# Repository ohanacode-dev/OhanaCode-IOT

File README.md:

**OhanaCode-IOT**

This is my personal Internet Of Things set of projects. It is intended as a low budget home automation system. 
I am building my own WiFi controlled devices and controlling them through their own web interface. 
Most devices can act as an access point or a client device on a WiFi network. After it connects to your home network, 
it gets difficult to find its IP address if it is dynamically alocated, so I also provided an Android app to list all devices on the same network. 
Every device responds to an UDP broadcast string "ujagaga ping" via TCP socket. 
There is also an implemented Over The Air update. 
Most projects are build using Arduino studio and an **ESP8266** device. I am using **Wemos D1 mini** and **ESP-12** devices.

NOTE: this is still work in progress. Most of the projects are functional, but I still want to improove them.
Most projects support "Over The Air" update, but it does sometimes crash, so you will still ocasionally need the wired connection.
The whole project is in the process if adding mqtt support in order to connect to the new addition "iot-portal". This way you can controll them all from a single device.

## Latest Changes

- Fixed LED_lamp_RGB project to use the iot-portal.

- Fixed "switch" project to use the iot-portal. Had to remove udp ping as it caused connection issues.

- Added iot-portal to be ran on a computer like raspberry pi zero. All devices should report to it so it can be used as a central point of access. 

---

## Using the code

Every device has an Arduino sketch in it's own folder, so open the sketch in **Arduino studio** and set the proper board and parameters for your board, compile and program. 
For the web interface some projects use SPIFFS library to upload HTML, CSS, JS files to virtual file system in the SPI flash. To upload these files, you need **Arduino ESP8266 filesystem uploader**. It integrates in your Arduino studio and adds an entry in the **Tools** menu. To install it, follow instructions from: https://github.com/esp8266/arduino-esp8266fs-plugin
After that you might want to open the **serial monitor** to see the debug messages for more info. 
You can then connect to devices access point, use your browser to control and configure it. 
Project is still in development. I believe that the switch, LED_lamp, LED_lamp_RGB, lazy_control and OC-IOT-Browser have reached their final state and are ready for use. Other projects are usable, but will be refactored a lot. Reffer to each projects **readme** for current status. 

---

## lazy_control

A python multimedial server for your PC. Should work on windows and linux.

---

## LED_lamp

Just a single color LED light controll device. 

---

## LED_lamp_RGB

An RGB LED lamp controll.

---

## NTP_clock

A stepper motor control using an NTP server for time sync. This will drive two clock hands to show time.

---

## NTP_timer

An NTP synchronized timer to activate a relay.

---

## thermometer

A thermometer using either low temperature probe **DS18B20** or a high temperature thermopar probe module with **max6675**.

---

## thermostat

A thermometer project expanded with a relay driving capability.

---

## IOTBrowser

An Android application to list and provide a quick access to all **Ohana-IOT** devices on the same network.

---

## ohana-radio

A linux internet radio with a web interface.

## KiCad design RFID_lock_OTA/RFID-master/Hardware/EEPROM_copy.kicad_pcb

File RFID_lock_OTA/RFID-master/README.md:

RFID reader project for AtTiny2313 using MIFARE RFID-RC522 spi module

The RFID library is based on Addicore arduino library. I re-wrote it as pure C library and removed 
everything not esential to bare reading of an RFID TAG id to reduce the code size.

The initial commit contains a basic example of reading a tag and outputting the 4 bytes of id to UART.
The latest commit contains:
- full RFID example which can record up to 32 tag ids and unlock an electromagnetic lock
- EEPROM reader device which can be used to record the RFID readers memory and write it back on command
so that re-distributing codes between multiple locks can be simpified
- Linux and Windows console applications for administrating tag ids using either the EEPROM copy device 
or the RFID reader directly.

more details will be in the doc folder.

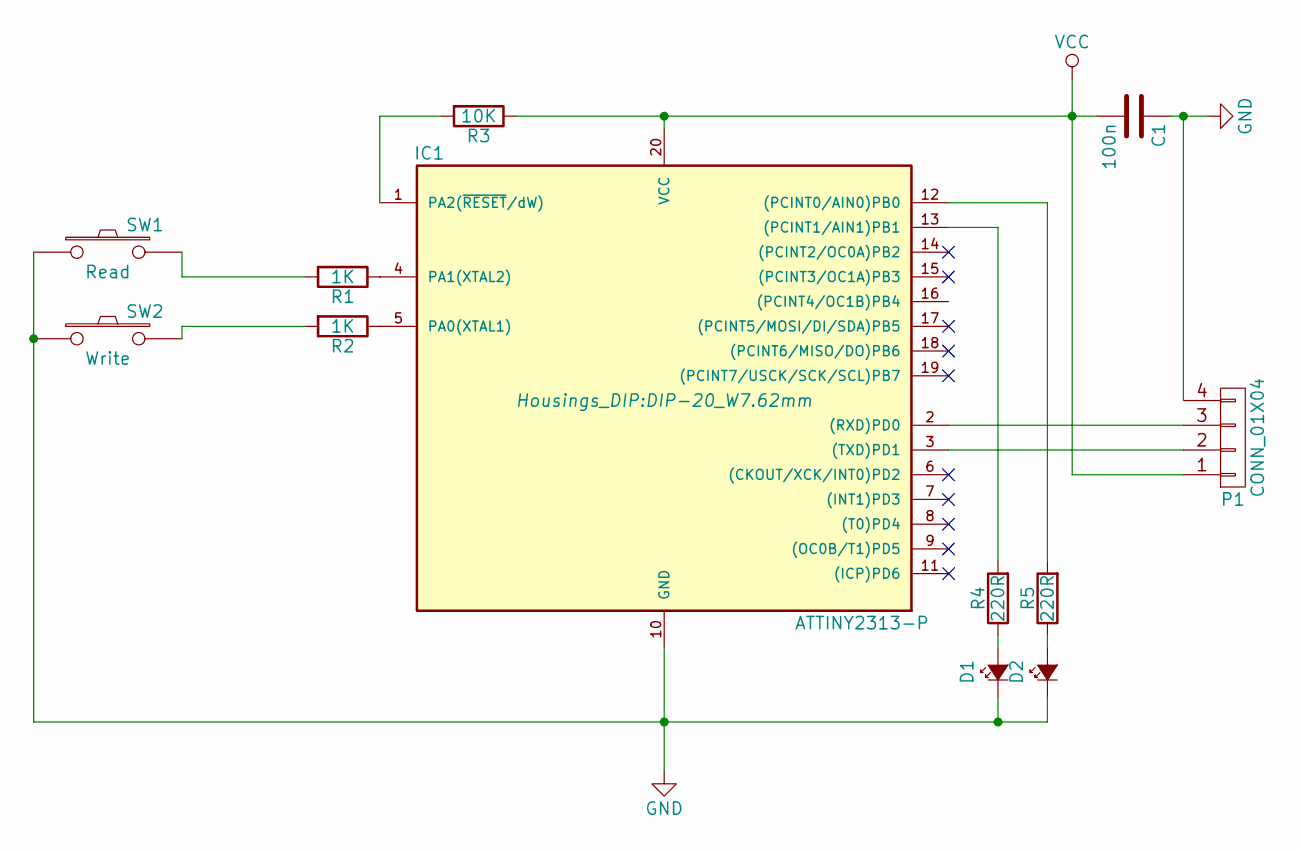
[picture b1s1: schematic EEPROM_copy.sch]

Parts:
C1: 100n; C_0805_HandSoldering
D1, D2: Led_Small; LED-3MM
IC1: ATTINY2313-P; DIP-20_W7.62mm
P1: CONN_01X04; Socket_Strip_Angled_1x04
R1, R2: 1K; R_0805
R3: 10K; R_0805
R4, R5: 220R; R_0805
SW1: Read; Micro_sw_1
SW2: Write; Micro_sw_1

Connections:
GND: C1.1, D1.1 (K), D2.1 (K), IC1.10 (GND), P1.4, SW1.1, SW2.1
unnamed: D1.2 (A), R4.1
unnamed: D2.2 (A), R5.1
unnamed: IC1.1 (PA2(~RESET~/dW)), R3.2
unnamed: IC1.2 ((RXD)PD0), P1.3
unnamed: IC1.3 ((TXD)PD1), P1.2
unnamed: IC1.4 (PA1(XTAL2)), R1.1
unnamed: IC1.5 (PA0(XTAL1)), R2.1
unnamed: IC1.12 ((PCINT0/AIN0)PB0), R5.2
unnamed: IC1.13 ((PCINT1/AIN1)PB1), R4.2
unnamed: R1.2, SW1.2
unnamed: R2.2, SW2.2
VCC: C1.2, IC1.20 (VCC), P1.1, R3.1

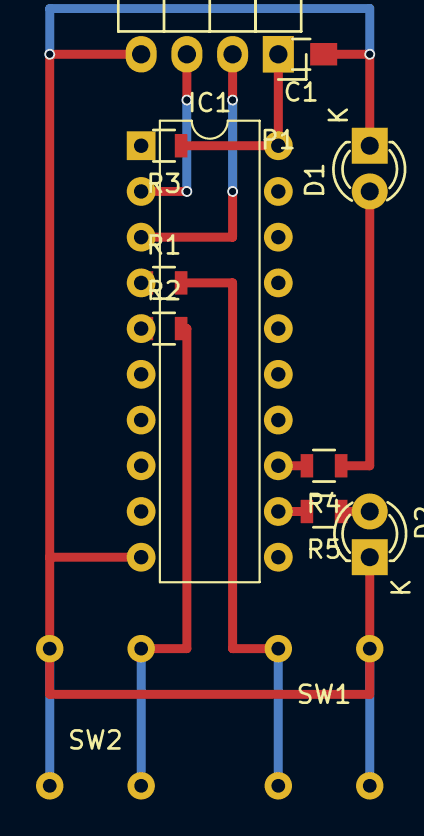
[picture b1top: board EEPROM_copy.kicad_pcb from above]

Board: 2 copper layers, 12 parts (0 on the bottom side), 13 nets.

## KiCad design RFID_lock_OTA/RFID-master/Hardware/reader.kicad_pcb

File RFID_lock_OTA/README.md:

# RFID lock

In progress. Not usable yet.

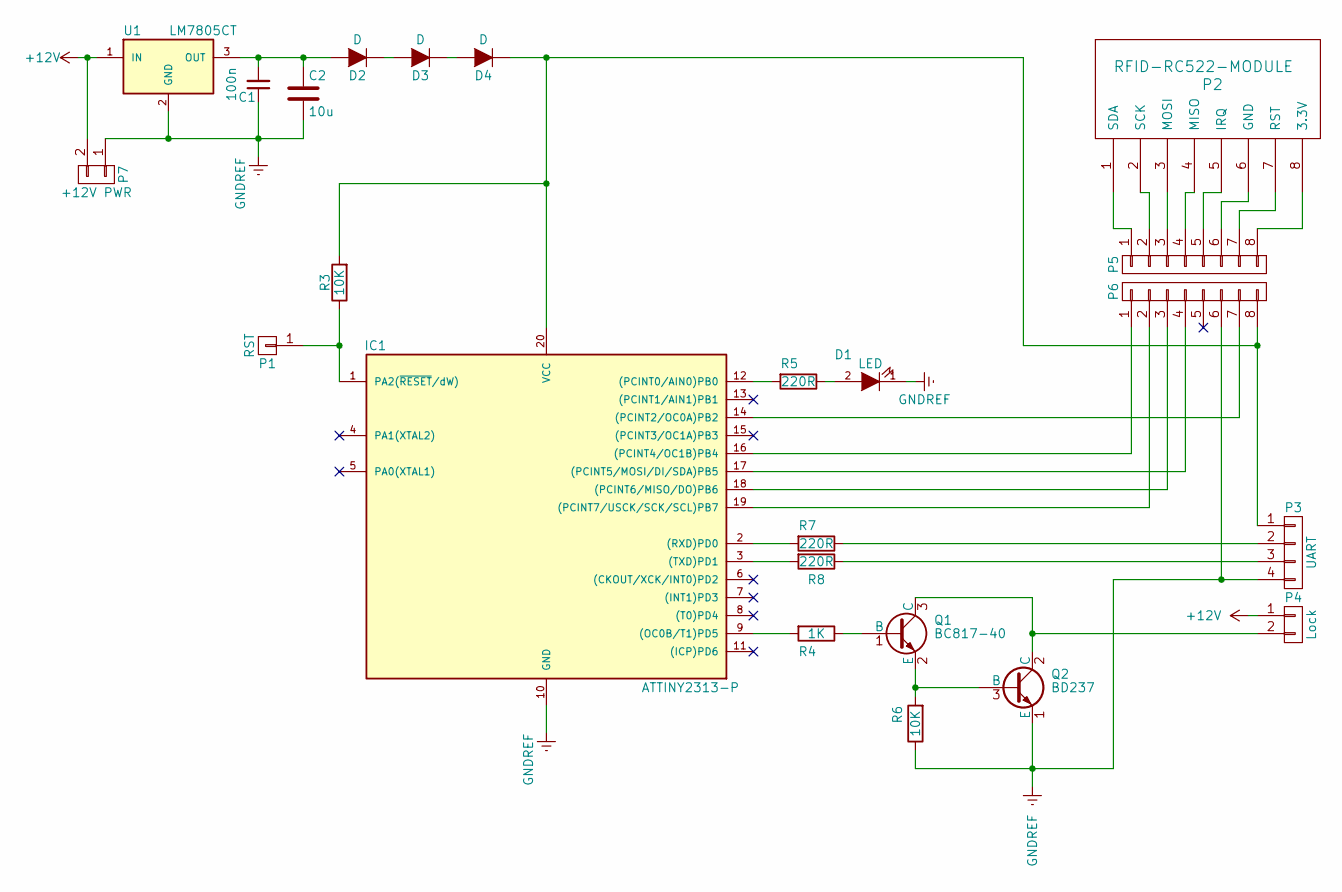
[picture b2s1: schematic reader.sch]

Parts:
C1: 100n; C_0805_HandSoldering
C2: 10u; C_0805_HandSoldering
D1: LED; LED-3MM
D2, D3, D4: D; D_0805
IC1: ATTINY2313-P; DIP-20_W7.62mm
P1: RST; Socket_Strip_Straight_1x01
P2: RFID-RC522-MODULE; Socket_Strip_Straight_1x08
P3: UART; Socket_Strip_Angled_1x04
P4: Lock; Socket_Strip_Straight_1x02
P5, P6: CONN_01X08; Socket_Strip_Straight_1x08
P7: +12V PWR; Socket_Strip_Straight_1x02
Q1: BC817-40; SOT-23
Q2: BD237; SOT126_SOT32_Housing_Vertical
R3, R6: 10K; R_0805_HandSoldering
R4: 1K; R_0805_HandSoldering
R5, R7, R8: 220R; R_0805_HandSoldering
U1: LM7805CT; TO-220

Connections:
+12V: P4.1, P7.2, U1.1 (IN)
GNDREF: C1.1, C2.2, D1.1 (K), IC1.10 (GND), P3.4, P6.6, P7.1, Q2.1 (E), R6.1, U1.2 (GND)
unnamed: C1.2, C2.1, D2.2 (A), U1.3 (OUT)
unnamed: D1.2 (A), R5.1
unnamed: D2.1 (K), D3.2 (A)
unnamed: D3.1 (K), D4.2 (A)
unnamed: D4.1 (K), IC1.20 (VCC), P3.1, P6.8, R3.2
unnamed: IC1.1 (PA2(~RESET~/dW)), P1.1, R3.1
unnamed: IC1.2 ((RXD)PD0), R7.2
unnamed: IC1.3 ((TXD)PD1), R8.2
unnamed: IC1.9 ((OC0B/T1)PD5), R4.2
unnamed: IC1.12 ((PCINT0/AIN0)PB0), R5.2
unnamed: IC1.14 ((PCINT2/OC0A)PB2), P6.7
unnamed: IC1.16 ((PCINT4/OC1B)PB4), P6.1
unnamed: IC1.17 ((PCINT5/MOSI/DI/SDA)PB5), P6.4
unnamed: IC1.18 ((PCINT6/MISO/DO)PB6), P6.3
unnamed: IC1.19 ((PCINT7/USCK/SCK/SCL)PB7), P6.2
unnamed: P2.1 (SDA), P5.1
unnamed: P2.2 (SCK), P5.2
unnamed: P2.3 (MOSI), P5.3
unnamed: P2.4 (MISO), P5.4
unnamed: P2.5 (IRQ), P5.5
unnamed: P2.6 (GND), P5.6
unnamed: P2.7 (RST), P5.7
unnamed: P2.8 (3.3V), P5.8
unnamed: P3.2, R7.1
unnamed: P3.3, R8.1
unnamed: P4.2, Q1.3 (C), Q2.2 (C)
unnamed: Q1.1 (B), R4.1
unnamed: Q1.2 (E), Q2.3 (B), R6.2

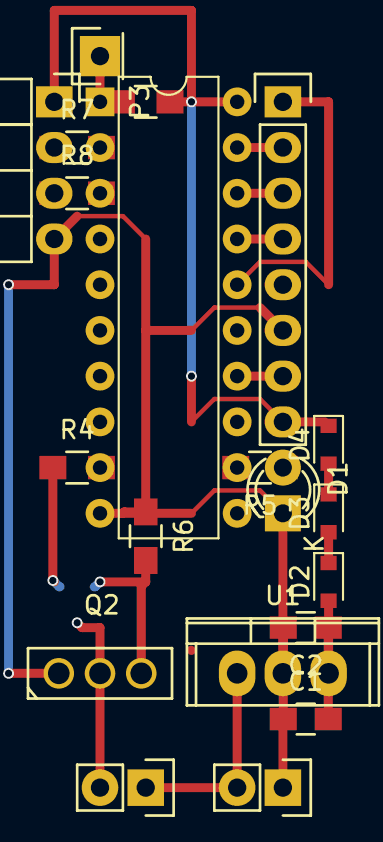
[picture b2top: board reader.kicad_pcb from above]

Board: 2 copper layers, 21 parts (1 on the bottom side), 22 nets.

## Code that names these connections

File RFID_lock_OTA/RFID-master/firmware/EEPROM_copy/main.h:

#ifndef MAIN_H
#define MAIN_H

#include <stdint.h>
#include <avr/io.h>
#include <avr/interrupt.h>
#include <stdint.h>
#include <stdbool.h>
#include <util/delay.h>
#include <avr/eeprom.h>


#define LED_GRN_PIN		PB0
#define LED_RED_PIN 	PB1
#define BTN_READ_PIN	PA0
#define BTN_WRITE_PIN	PA1

#endif

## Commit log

2019-11-19 Updated logo, readme and branding
2019-11-19 Add hub
2019-11-19 Got hub detecting devices
2019-11-20 Minor comment
2019-11-20 Branding and hub UI
2019-11-21 UI change
2019-11-24 HUB in progress
2019-11-25 Finished labels
2019-12-01 Add switch
2019-12-01 Updated hub
2019-12-01 Updated switch
2019-12-01 Updated schematic
2019-12-01 Add pushbutton support
2019-12-04 Updated LED_lamp
2019-12-07 New lamp interface
2019-12-09 Improoved LED lamp UI
2019-12-13 Updated LED UI
2019-12-13 Add touch support
2020-01-10 Add WiFi keyboard
2020-01-13 New NTP clock
2020-01-14 Finished NTP clock basic
2020-01-14 New timer in progress
2020-01-15 Completing table entry
2020-01-15 Updated NTP clk w
2020-01-15 NTP timer w working
2020-01-16 Not so great
2020-01-17 Working
2020-06-30 Updated IOTBrowser
2020-07-03 Updated radio app
2020-07-04 Fixed IOT browser
2020-07-04 Add list sort function
2020-07-04 Better style
2020-07-04 Add ip addr
2020-07-05 Improovements
2020-07-06 Add save pls
2020-08-11 Merge
2020-08-12 Updated radio readme
2020-08-14 Add GPIO control for radio
2020-08-14 Linux box streaming instructions added
2020-08-14 Improoved gpiocmd.py
2020-08-21 Add multimedia control
2020-08-27 mm_ctrl
2020-08-27 Add scan
2020-08-28 Finished first version of mm_client
2020-08-28 Finished mm client
2020-08-29 Client improovemetns
2020-09-01 mm control upgrade
2020-09-01 Switched to mouse click
2020-09-03 Good mm_control version
2020-09-03 Test
2020-09-03 Good version
2020-09-03 Best mm_ctrl version yet
2020-09-04 Adding shell installer
2020-09-04 New icons
2020-09-09 Add linux mm_ctrl installer
2020-09-11 mm_ctrl Switched to UDP only
2020-09-12 mm_ctrl new server installer
2020-12-09 Changed RGB UI to sliders
2020-12-24 Add NTP windmill and UART emulator
2020-12-25 Finished the windmill
2020-12-25 Attached windmill 7-segment fw
2020-12-28 New motor driver
2020-12-29 Updated clock step
2021-05-08 Latest changes
2021-07-12 Add iot-portal
2021-07-13 Add thermometer
2021-07-14 initial functional version
2021-09-19 Switching to LittleFS
2021-09-20 Improoved iot portal
2021-09-20 Oled driver startup service
2021-09-20 Oled improovement
2021-09-20 Reduced weather query frequency
2021-09-21 Finished weather and temperature for IOT portal
2021-09-21 Service fix
2021-09-21 Updated installer and added uninstaller for IOT portal
2021-09-22 Adjusting switch for mqtt
2021-09-23 Finalized switch project with mqtt support
2021-09-23 Finished switch
2021-09-23 Add gpio btn service
2021-10-05 RGB fixed
2021-10-05 Updated RGB
2021-10-05 Fixed LED lamp color save
2021-10-11 Adding remove btn
2021-10-11 IOT portal add device remove
2021-10-14 Updated readme for iot-portal
2021-10-29 New battery operated thermometer
2021-10-30 iot-portal oled driver msg validat
2022-04-02 Update mac of iot-portal slave
2022-04-02 Add python3-pip to iot install
2022-04-02 Install fix
2022-04-03 Updated weather
2022-04-03 correction
2022-04-05 Updated weathen
2022-07-21 Add neopixedl
2022-07-23 No FS html
2023-02-14 Bump starlette from 0.14.2 to 0.25.0 in /iot-portal
    Bumps [starlette](https://github.com/encode/starlette) from 0.14.2 to 0.25.0.
    - [Release notes](https://github.com/encode/starlette/releases)
    - [Changelog](https://github.com/encode/starlette/blob/master/docs/release-notes.md)
    - [Commits](https://github.com/encode/starlette/compare/0.14.2...0.25.0)
    ---
    updated-dependencies:
2025-03-23 Simplified Neopixel LED
